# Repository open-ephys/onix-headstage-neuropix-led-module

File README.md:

# ONIX Neuropixels tracking LED module
Flex PCB desings for adding LEDs to ONIX neuropixels headstages
for color-based video tracking.

- Design 1: Two surface mount LEDs spaced by 30 mm.
- Design 2: A 1-mm pitch socket exposes pins for up to 3 tracking LEDs that
  can be attached by the user. 

## Hardware License
[CC BY-NC-SA](https://creativecommons.org/licenses/by-nc-sa/4.0)

The creation of commercial products using the hardware documentation in this
repository is not permitted without an explicit, supplementary agreement
between the Licensor and the Licensee. Please get in touch if you are
interested in commercially distributing this tool.

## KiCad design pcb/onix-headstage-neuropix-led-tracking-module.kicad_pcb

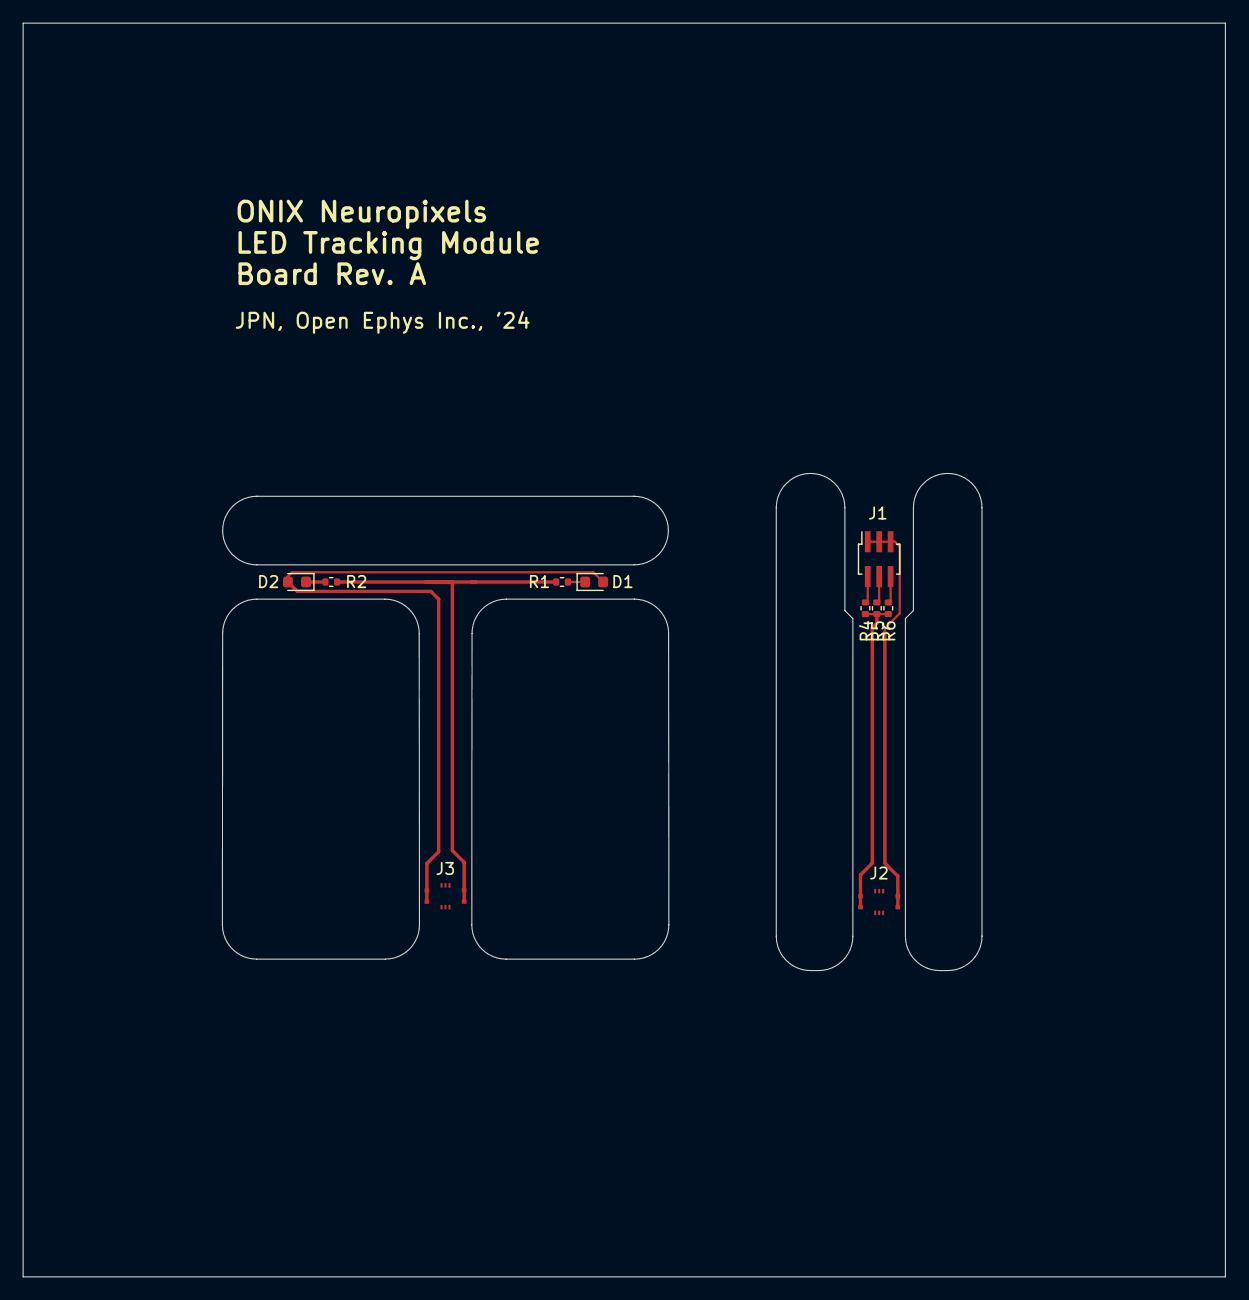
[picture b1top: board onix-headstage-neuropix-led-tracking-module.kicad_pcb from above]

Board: 2 copper layers, 105.2 x 109.7 mm, 10 parts (0 on the bottom side), 9 nets.

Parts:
D1, D2: LED; LED_0603_1608Metric
J1: Conn_02x03_Odd_Even; PinSocket_2x03_P1.00mm_Vertical_SMD
J2, J3: 5050660622; MOLEX_5050660622
R1, R2, R4, R5, R6: 1k; R_0402_1005Metric

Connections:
+4V: D1.2 (A), D2.2 (A), J2.MP1 (MountPin1), J2.MP2 (MountPin2), J3.MP1 (MountPin1), J3.MP2 (MountPin2), R4.2, R5.2, R6.2
/SCL: J2.1, J3.1
/SDA: J2.3, J3.3
GND: J1.1, J1.3, J1.5, J2.MP3 (MountPin3), J2.MP4 (MountPin4), J3.MP3 (MountPin3), J3.MP4 (MountPin4), R1.1, R2.1
unnamed: D1.1 (K), R1.2
unnamed: D2.1 (K), R2.2
unnamed: J1.2, R4.1
unnamed: J1.4, R5.1
unnamed: J1.6, R6.1

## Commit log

2024-11-18 Update README.md
    - Fix typos
    - Update design description
